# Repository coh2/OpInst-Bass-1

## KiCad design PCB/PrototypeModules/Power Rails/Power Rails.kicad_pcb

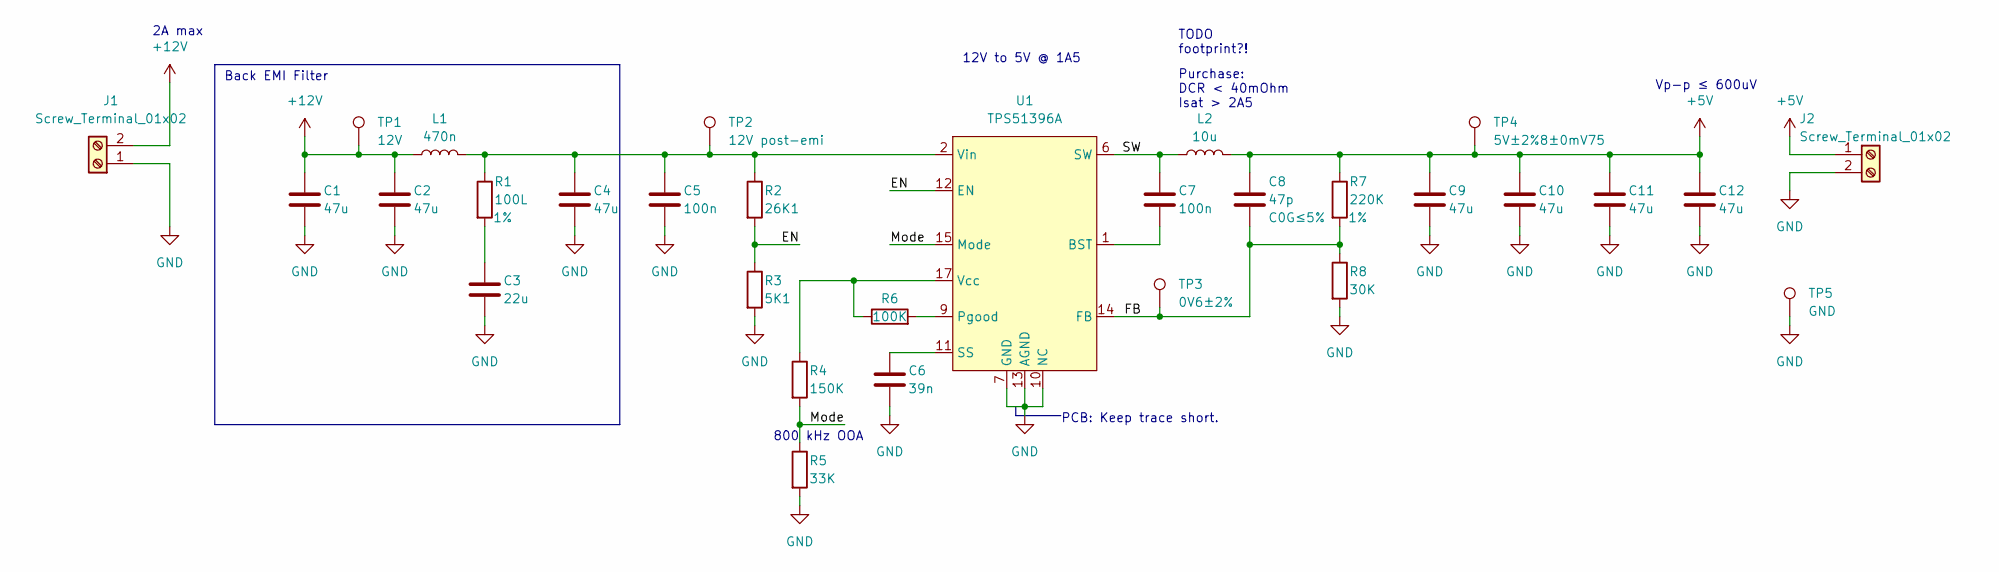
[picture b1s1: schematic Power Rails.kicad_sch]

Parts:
C1, C2, C4, C9, C10, C11, C12: 47u; C_1210_3225Metric_Pad1.33x2.70mm_HandSolder
C3: 22u; R_0805_2012Metric_Pad1.20x1.40mm_HandSolder
C5, C7: 100n; C_0402_1005Metric_Pad0.74x0.62mm_HandSolder
C6: 39n; C_0402_1005Metric_Pad0.74x0.62mm_HandSolder
C8: 47p; C_0402_1005Metric_Pad0.74x0.62mm_HandSolder; Tolerance C0G≤5%
J1, J2: Screw_Terminal_01x02; TerminalBlock_bornier-2_P5.08mm
L1: 470n; L_Taiyo-Yuden_NR-50xx_HandSoldering
L2: 10u; L_Taiyo-Yuden_NR-80xx_HandSoldering
R1: 100L; R_1206_3216Metric_Pad1.30x1.75mm_HandSolder; Tolerance 1%
R2: 26K1; R_0603_1608Metric_Pad0.98x0.95mm_HandSolder
R3: 5K1; R_0603_1608Metric_Pad0.98x0.95mm_HandSolder
R4: 150K; R_0603_1608Metric_Pad0.98x0.95mm_HandSolder
R5: 33K; R_0603_1608Metric_Pad0.98x0.95mm_HandSolder
R6: 100K; R_0603_1608Metric_Pad0.98x0.95mm_HandSolder
R7: 220K; R_0603_1608Metric_Pad0.98x0.95mm_HandSolder; Tolerance 1%
R8: 30K; R_0603_1608Metric_Pad0.98x0.95mm_HandSolder; Tolerance 1%
TP1: 12V; TestPoint_Pad_3.0x3.0mm
TP2: 12V post-emi; TestPoint_Pad_3.0x3.0mm
TP3: 0V6±2%; TestPoint_Pad_3.0x3.0mm
TP4: 5V±2%8±0mV75; TestPoint_Pad_3.0x3.0mm
TP5: GND; TestPoint_Pad_3.0x3.0mm
U1: TPS51396A; VQFN-20-1EP_3x3mm_P0.45mm_EP1.55x1.55mm_ThermalVias

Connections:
+5V: C8.1, C9.1, C10.1, C11.1, C12.1, J2.1, L2.2, R7.1, TP4.1
+12V: C1.1, C2.1, J1.2, L1.1, TP1.1
/EN: R2.2, R3.1, U1.12 (EN)
/FB: C8.2, R7.2, R8.1, TP3.1, U1.14 (FB)
/Mode: R4.2, R5.1, U1.15 (Mode)
/SW: C7.1, L2.1, U1.6 (SW), U1.19 (SW), U1.20 (SW)
GND: C1.2, C2.2, C3.2, C4.2, C5.2, C6.2, C9.2, C10.2, C11.2, C12.2, J1.1, J2.2, R3.2, R5.2, R8.2, TP5.1, U1.7 (GND), U1.8 (GND), U1.10 (NC), U1.13 (AGND), U1.16 (NC), U1.18 (GND), U1.21 (GND)
unnamed: C3.1, R1.2
unnamed: C6.1, U1.11 (SS)
unnamed: C7.2, U1.1 (BST)
unnamed: R4.1, R6.1, U1.17 (Vcc)
unnamed: R6.2, U1.9 (Pgood)
Vin: C4.1, C5.1, L1.2, R1.1, R2.1, TP2.1, U1.2 (Vin), U1.3 (Vin), U1.4 (Vin), U1.5 (Vin)

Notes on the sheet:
2A max
Back EMI Filter
800 kHz OOA
12V to 5V @ 1A5
PCB: Keep trace short.
TODO footprint?!
Purchase: DCR < 40mOhm Isat > 2A5
Vp-p ≤ 600uV

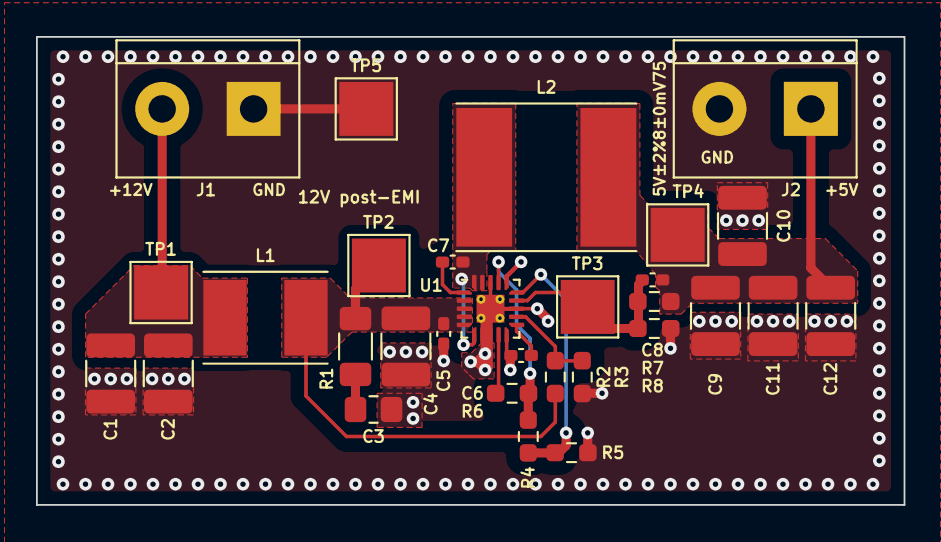
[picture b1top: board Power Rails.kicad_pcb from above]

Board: 2 copper layers, 48.2 x 26.0 mm, 30 parts (0 on the bottom side), 13 nets.

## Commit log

2021-10-03 12V->5V prototype board done
